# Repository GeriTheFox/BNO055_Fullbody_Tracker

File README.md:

# BNO055_Fullbody_Tracker
 Based on the [SlimeVR](https://github.com/SlimeVR/) project
 
## THis project was work in prograss, build with your own risk.

The pcb based on the [BNO055](https://cdn-shop.adafruit.com/datasheets/BST_BNO055_DS000_12.pdf) Sensor, and the [ESP8266-12F](https://docs.ai-thinker.com/_media/esp8266/docs/esp-12f_product_specification_en.pdf). Designed in the open source [KiCad](https://www.kicad.org/) software.

The design should be compatibile with the original [limeVR-Tracker-ESP](https://github.com/SlimeVR/SlimeVR-Tracker-ESP) project.

The only reason this project exist cuz i got a bunch of BNO055 from a university, so i decied to make something useful lookinng from it.

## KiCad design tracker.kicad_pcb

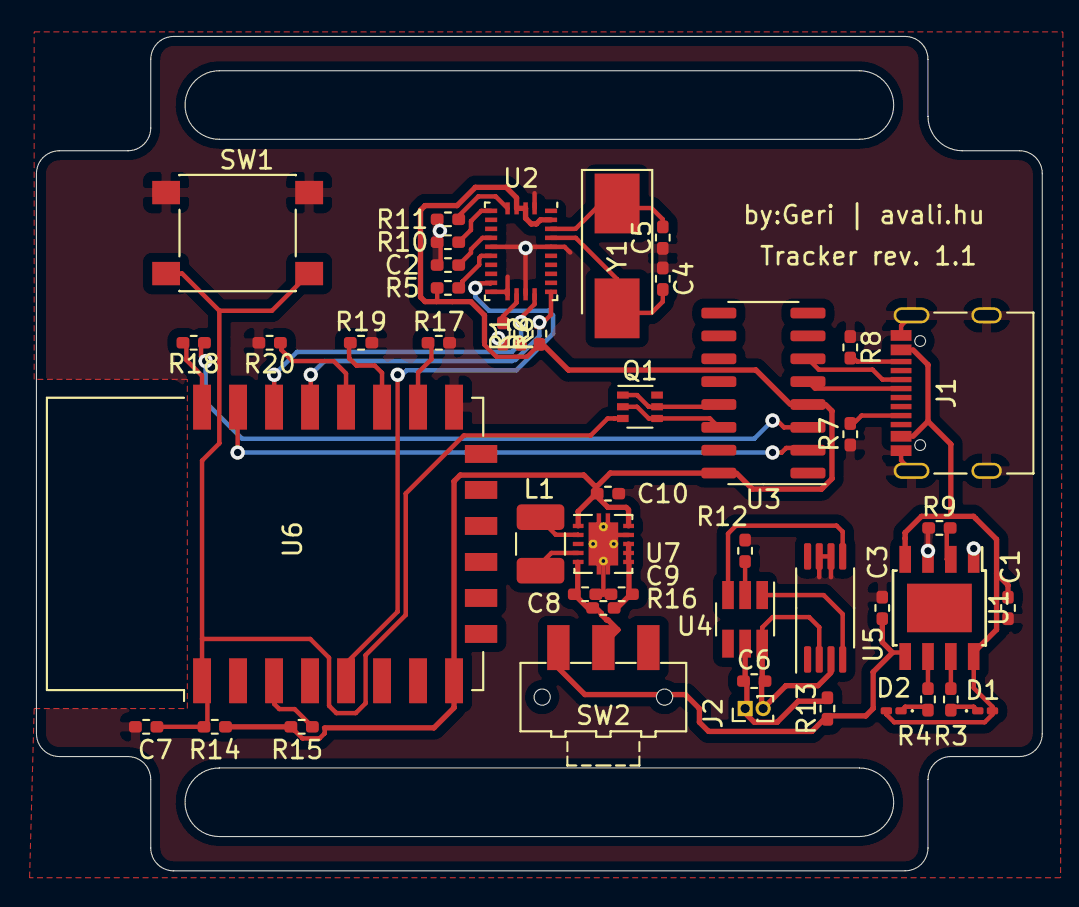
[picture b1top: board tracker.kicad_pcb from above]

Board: 2 copper layers, 55.9 x 46.4 mm, 46 parts (0 on the bottom side), 42 nets.

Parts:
C1, C2, C6, C8, C9, C10: 0.1 uF; R_0402_1005Metric_Pad0.72x0.64mm_HandSolder
C3: 10 uF; R_0402_1005Metric_Pad0.72x0.64mm_HandSolder
C4, C5: 22 pF; R_0402_1005Metric_Pad0.72x0.64mm_HandSolder
C7: 100 nF; R_0402_1005Metric_Pad0.72x0.64mm_HandSolder
D1, D2: LED; LED_0201_0603Metric_Pad0.64x0.40mm_HandSolder
J1: USB_C_Receptacle_USB2.0; USB_C_Receptacle_Palconn_UTC16-G
J2: BAT; PinHeader_1x02_P1.00mm_Vertical
L1: 2.2uH; L_1210_3225Metric_Pad1.42x2.65mm_HandSolder
Q1: UMH3N; SOT-363_SC-70-6
R1, R2, R5, R6, R9, R10, R11: 10K; R_0402_1005Metric_Pad0.72x0.64mm_HandSolder
R3, R4, R12: 1K; R_0402_1005Metric_Pad0.72x0.64mm_HandSolder
R7, R8: 5.1K; R_0402_1005Metric_Pad0.72x0.64mm_HandSolder
R13, R16: 100; R_0402_1005Metric_Pad0.72x0.64mm_HandSolder
R14, R15, R17, R19, R20: 12K; R_0402_1005Metric_Pad0.72x0.64mm_HandSolder
R18: 470; R_0402_1005Metric_Pad0.72x0.64mm_HandSolder
SW1: SW_Push; SW_Push_1P1T_NO_6x6mm_H9.5mm
SW2: PWR_SW; SW_SPDT_CK-JS102011SAQN
U1: TP4056; TP4056_SOP-8-PP
U2: BNO055; LGA-28_5.2x3.8mm_P0.5mm
U3: CH340C; SOIC-16_3.9x9.9mm_P1.27mm
U4: DW01; SOT-23-6_Handsoldering
U5: FS8205A; TSSOP-8_4.4x3mm_P0.65mm
U6: ESP-12F; ESP-12E
U7: TPS63001; Texas_DRC0010J_ThermalVias
Y1: 32.768 Khz; Crystal_SMD_0603-2Pin_6.0x3.5mm_HandSoldering

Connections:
+3V3: C10.2, R1.1, R2.1, R5.2, R14.1, R15.1, U2.3, U2.4, U2.28, U3.4, U3.16, U6.8, U7.1, U7.10
+5V: C1.2, D1.2, D2.2, J1.A4, J1.A9, J1.B4, J1.B9, U1.4, U1.8
DTR: Q1.1, Q1.5, U3.13
GND: C1.1, C2.1, C3.2, C4.1, C5.1, C7.2, C8.1, C9.1, C10.1, J1.A1, J1.A12, J1.B1, J1.B12, J1.S1, R6.2, R7.1, R8.1, R9.1, R10.1, R11.1, R12.1, R17.2, R19.2, R20.2, SW1.1, U1.1, U1.3, U2.2, U2.10, U2.15, U2.16, U2.18, U2.25, U5.6, U5.7, U6.15, U7.3, U7.9, U7.11
INT: U2.14, U6.5
unnamed: C2.2, U2.9
unnamed: C3.1, R13.1, SW2.1, U1.5
unnamed: C4.2, U2.26, Y1.2
unnamed: C5.2, U2.27, Y1.1
unnamed: C6.1, J2.1, R13.2, U4.5
unnamed: C6.2, J2.2, U4.6, U5.2, U5.3
unnamed: C8.2, R16.2, SW2.2, U7.5
unnamed: C9.2, R16.1, U7.6, U7.7, U7.8
unnamed: D1.1, R3.2
unnamed: D2.1, R4.2
unnamed: J1.A5, R7.2
unnamed: J1.A6, J1.B6, U3.6
unnamed: J1.A7, J1.B7, U3.5
unnamed: J1.B5, R8.2
unnamed: L1.1, U7.4
unnamed: L1.2, U7.2
unnamed: R3.1, U1.7
unnamed: R4.1, U1.6
unnamed: R5.1, U2.11
unnamed: R6.1, U2.17
unnamed: R9.2, U1.2
unnamed: R10.2, U2.6
unnamed: R11.2, U2.5
unnamed: R12.2, U4.2
unnamed: R15.2, U6.3
unnamed: R17.1, U6.16
unnamed: R18.2, U6.22
unnamed: R19.1, U6.17
unnamed: R20.1, U6.18
unnamed: U4.1, U5.4
unnamed: U4.3, U5.5
RST: C7.1, Q1.3, R14.2, SW1.2, U6.1
RTS: Q1.2, Q1.4, U3.14
RX: U3.2, U6.21
SCL: R1.2, U2.19, U6.20
SDA: R2.2, U2.20, U6.19
TX: R18.1, U3.3

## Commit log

2021-12-08 rev0
2021-12-11 REV1.1
2021-12-11 metric/imperial fix
